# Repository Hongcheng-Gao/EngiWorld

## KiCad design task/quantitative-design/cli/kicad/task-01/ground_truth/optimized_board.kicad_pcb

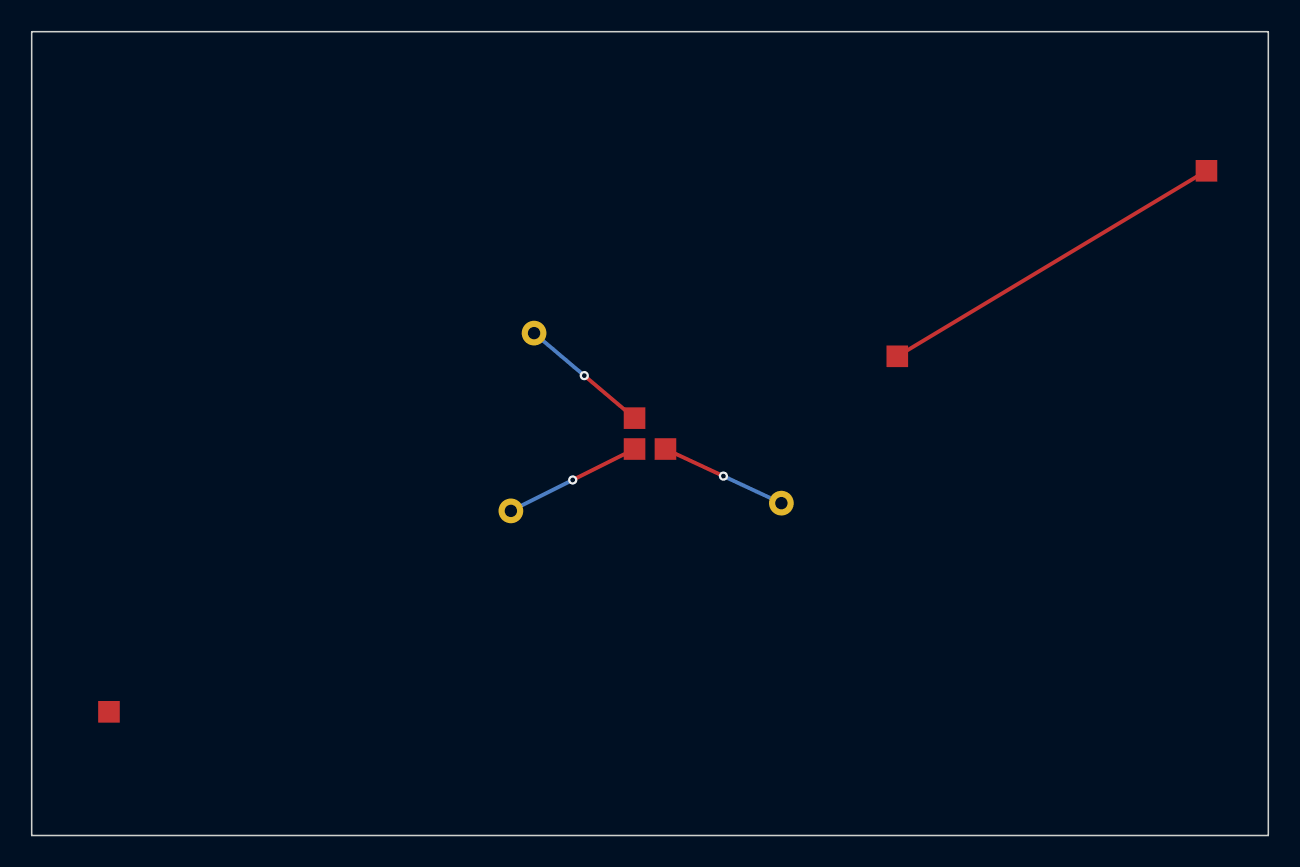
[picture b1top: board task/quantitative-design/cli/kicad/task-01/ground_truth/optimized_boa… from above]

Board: 2 copper layers, 80.0 x 52.0 mm, 7 parts (0 on the bottom side), 4 nets.

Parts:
C1, C2: 100nF
C3: 1uF
J1: INPUT
J2: OUTPUT
L1: 10uH
U1: MIXED_SIGNAL_MCU

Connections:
C1_U1: C1.1, U1.1
C2_U1: C2.1, U1.2
C3_U1: C3.1, U1.3
L1_J2: J2.1, L1.1

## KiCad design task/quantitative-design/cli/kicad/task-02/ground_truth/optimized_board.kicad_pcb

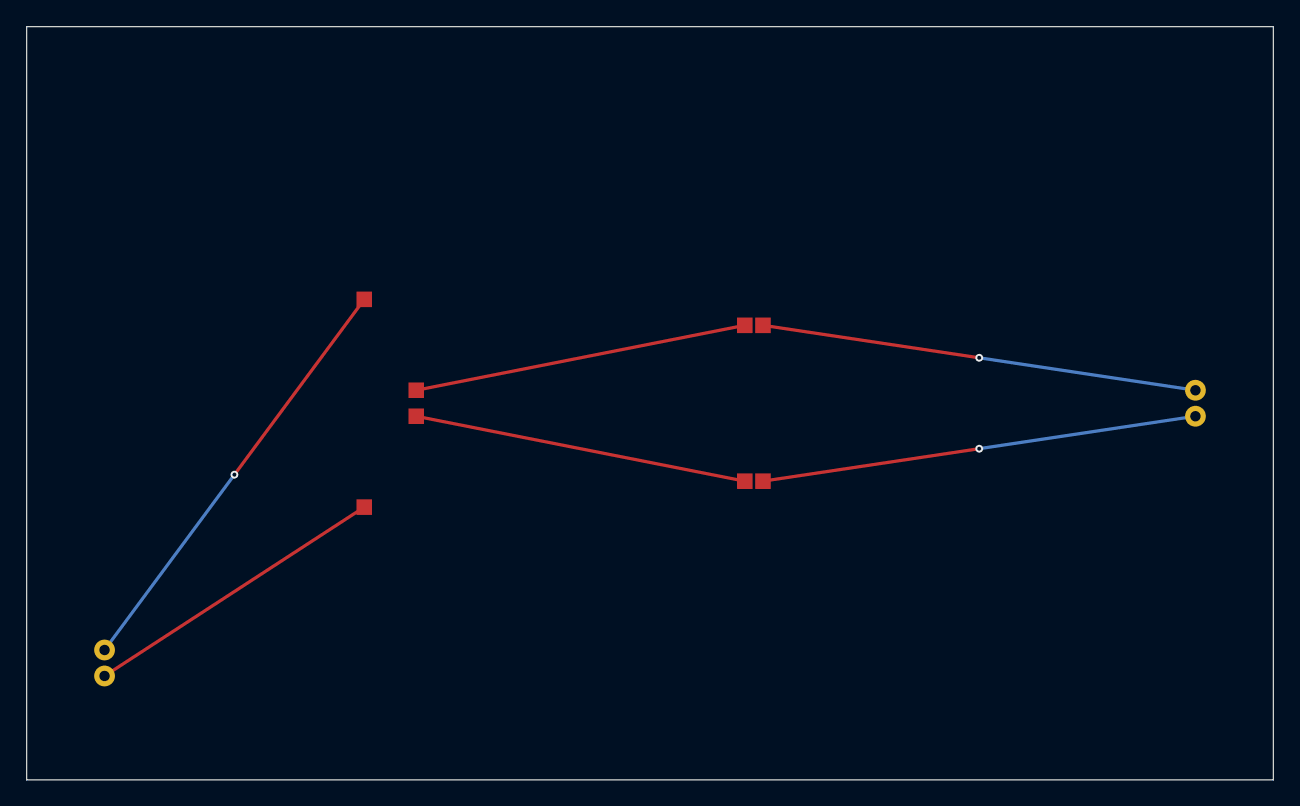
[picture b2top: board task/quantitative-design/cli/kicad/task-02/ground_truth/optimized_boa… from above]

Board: 2 copper layers, 96.0 x 58.0 mm, 7 parts (0 on the bottom side), 6 nets.

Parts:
C1, C2: 100nF
J1: DIFF_CONNECTOR
J2: BYPASS_CONNECTOR
R1, R2: 49.9R
U1: DIFF_DRIVER

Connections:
J2_C1: C1.1, J2.1
J2_C2: C2.1, J2.2
R1_J1: J1.1, R1.2
R2_J1: J1.2, R2.2
U1_R1: R1.1, U1.1
U1_R2: R2.1, U1.2

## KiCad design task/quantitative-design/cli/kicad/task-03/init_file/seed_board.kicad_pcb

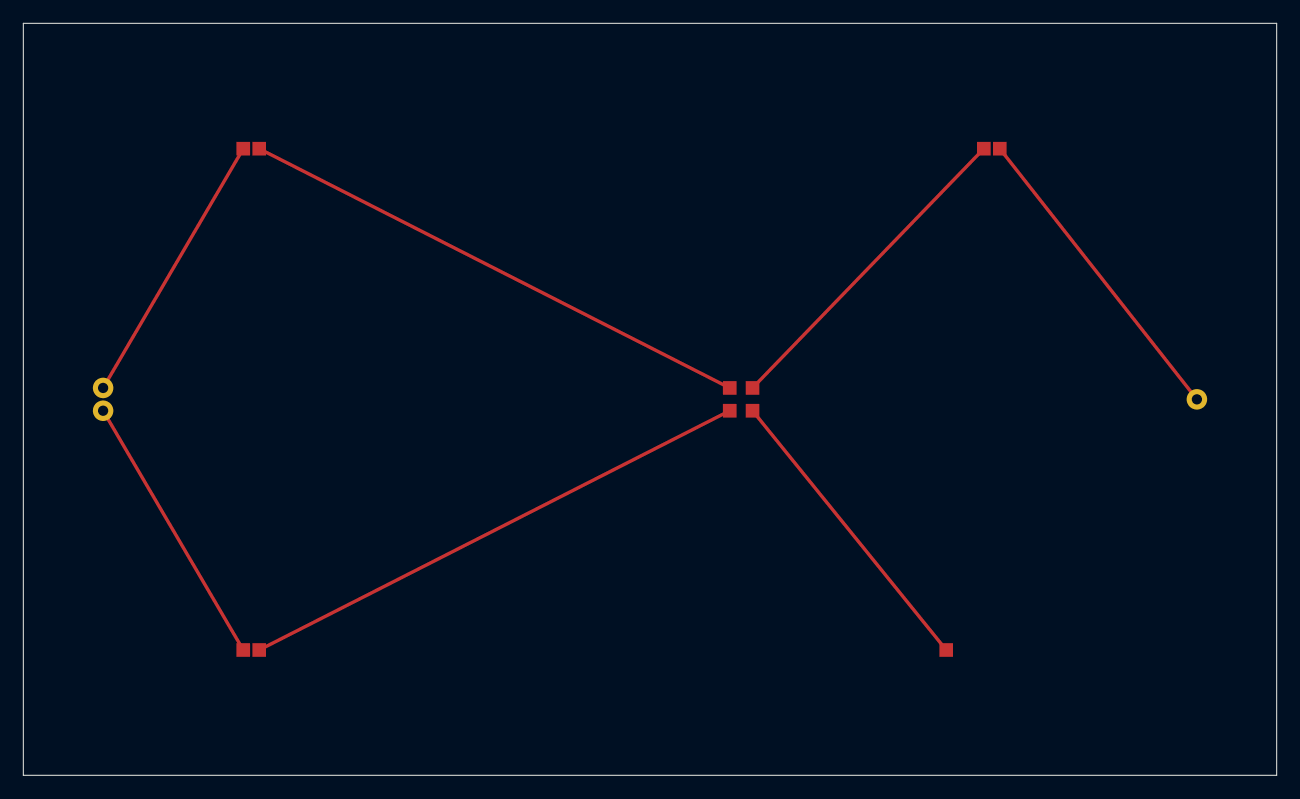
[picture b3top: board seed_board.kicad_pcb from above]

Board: 2 copper layers, 110.0 x 66.0 mm, 7 parts (0 on the bottom side), 7 nets.

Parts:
CIN1, CIN2: 47uF
D1: SCHOTTKY
J1: POWER_IN
J2: POWER_OUT
L1: 22uH
U1: REGULATOR

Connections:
CIN1_U1: CIN1.2, U1.1
CIN2_U1: CIN2.2, U1.2
J1_CIN1: CIN1.1, J1.1
J1_CIN2: CIN2.1, J1.2
L1_J2: J2.1, L1.2
U1_D1: D1.1, U1.3
U1_L1: L1.1, U1.4

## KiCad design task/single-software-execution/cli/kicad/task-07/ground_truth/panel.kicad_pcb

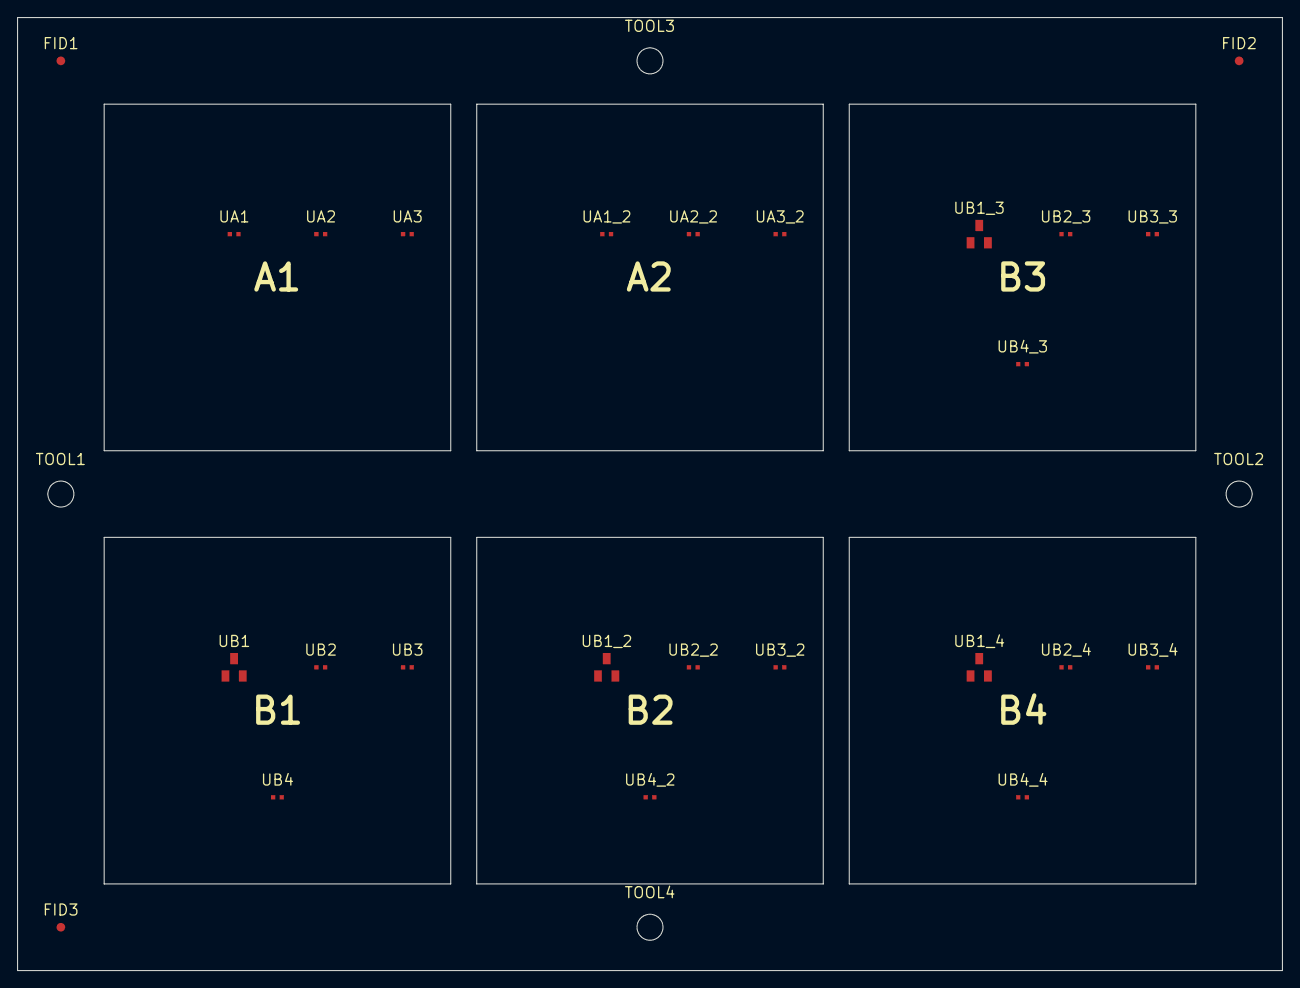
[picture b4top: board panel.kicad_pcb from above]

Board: 2 copper layers, 146.0 x 110.0 mm, 29 parts (0 on the bottom side), 4 nets, no tracks yet.

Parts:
FID1, FID2, FID3: Fiducial; Fiducial_1mm_Mask2mm
TOOL1, TOOL2, TOOL3, TOOL4: NPTH 3.0mm; MountingHole_3.0mm
UA1, UA1_2: 10k; R_0402_1005Metric
UA2, UA2_2: 22k; R_0402_1005Metric
UA3, UA3_2: 100nF; C_0402_1005Metric
UB1, UB1_2, UB1_3, UB1_4: 2N3904; SOT-23
UB2, UB2_2, UB2_3, UB2_4: 4.7k; R_0402_1005Metric
UB3, UB3_2, UB3_3, UB3_4: 1k; R_0402_1005Metric
UB4, UB4_2, UB4_3, UB4_4: 10nF; C_0402_1005Metric

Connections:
GND: UA1.2, UA1_2.2, UA2.2, UA2_2.2, UA3.2, UA3_2.2, UB1.1, UB1_2.1, UB1_3.1, UB1_4.1, UB3.2, UB3_2.2, UB3_3.2, UB3_4.2, UB4.2, UB4_2.2, UB4_3.2, UB4_4.2
PWR: UB1.2, UB1_2.2, UB1_3.2, UB1_4.2, UB2.1, UB2_2.1, UB2_3.1, UB2_4.1, UB4.1, UB4_2.1, UB4_3.1, UB4_4.1
SIG: UB1.3, UB1_2.3, UB1_3.3, UB1_4.3, UB2.2, UB2_2.2, UB2_3.2, UB2_4.2, UB3.1, UB3_2.1, UB3_3.1, UB3_4.1
VCC: UA1.1, UA1_2.1, UA2.1, UA2_2.1, UA3.1, UA3_2.1
